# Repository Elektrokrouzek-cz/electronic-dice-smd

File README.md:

# Electronic dice - SMD
This is the construction of electronic dice with SMD components. It is based on ATTINY24A microcontroller.

PCB is 2-layer and was designed using KiCad 9. Fabrication output for JLCPCB is in gerber folder.

Happy soldering!

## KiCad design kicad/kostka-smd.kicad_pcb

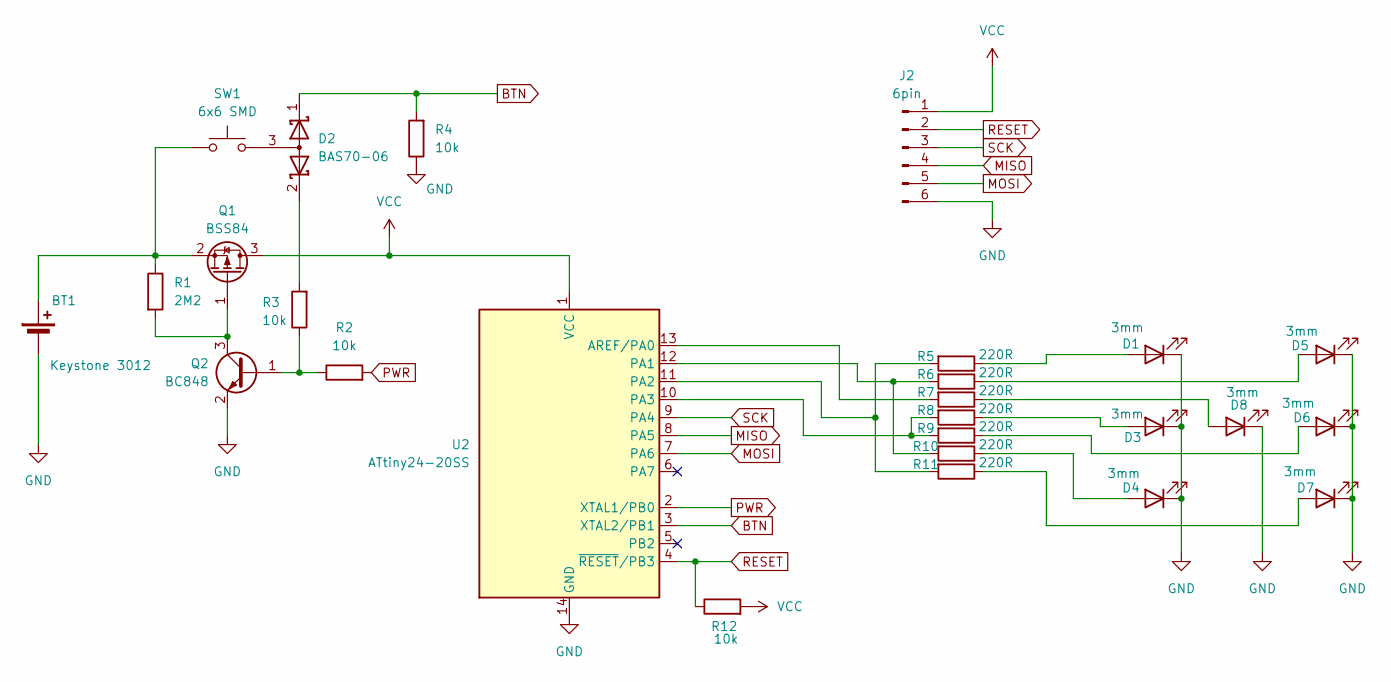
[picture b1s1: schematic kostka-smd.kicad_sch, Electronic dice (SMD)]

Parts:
BT1: Keystone 3012
D1, D3, D4, D5, D6, D7, D8: 3mm; LED_D3.0mm
D2: BAS70-06; SOT-23_Handsoldering
J2: 6pin; PinHeader_1x06_P2.54mm_Vertical
Q1: BSS84; SOT-23_Handsoldering
Q2: BC848; SOT-23_Handsoldering
R1: 2M2; R_1206_3216Metric_Pad1.30x1.75mm_HandSolder
R2, R3, R4, R12: 10k; R_1206_3216Metric_Pad1.30x1.75mm_HandSolder
R5, R6, R7, R8, R9, R10, R11: 220R; R_1206_3216Metric_Pad1.30x1.75mm_HandSolder
SW1: 6x6 SMD; SW_SPST_PTS645
U2: ATtiny24-20SS; SOIC-14_3.9x8.7mm_P1.27mm

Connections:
BTN: D2.1 (K), R4.2, U2.3 (XTAL2/PB1)
GND: BT1.2 (-), D1.1 (K), D3.1 (K), D4.1 (K), D5.1 (K), D6.1 (K), D7.1 (K), D8.1 (K), J2.6, Q2.2 (E), R4.1, U2.14 (GND)
MISO: J2.4, U2.8 (PA5)
MOSI: J2.5, U2.7 (PA6)
unnamed: BT1.1 (+), Q1.2 (S), R1.1, SW1.1
unnamed: D1.2 (A), R5.1
unnamed: D2.3 (A), SW1.2
unnamed: D2.2 (K), R3.2
unnamed: D3.2 (A), R8.1
unnamed: D4.2 (A), R10.1
unnamed: D5.2 (A), R6.1
unnamed: D6.2 (A), R9.1
unnamed: D7.2 (A), R11.1
unnamed: D8.2 (A), R7.1
unnamed: Q1.1 (G), Q2.3 (C), R1.2
unnamed: Q2.1 (B), R2.1, R3.1
unnamed: R7.2, U2.13 (AREF/PA0)
unnamed: R6.2, R10.2, U2.12 (PA1)
unnamed: R5.2, R11.2, U2.11 (PA2)
unnamed: R8.2, R9.2, U2.10 (PA3)
PWR: R2.2, U2.2 (XTAL1/PB0)
RESET: J2.2, R12.1, U2.4 (~RESET/PB3)
SCK: J2.3, U2.9 (PA4)
VCC: J2.1, Q1.3 (D), R12.2, U2.1 (VCC)

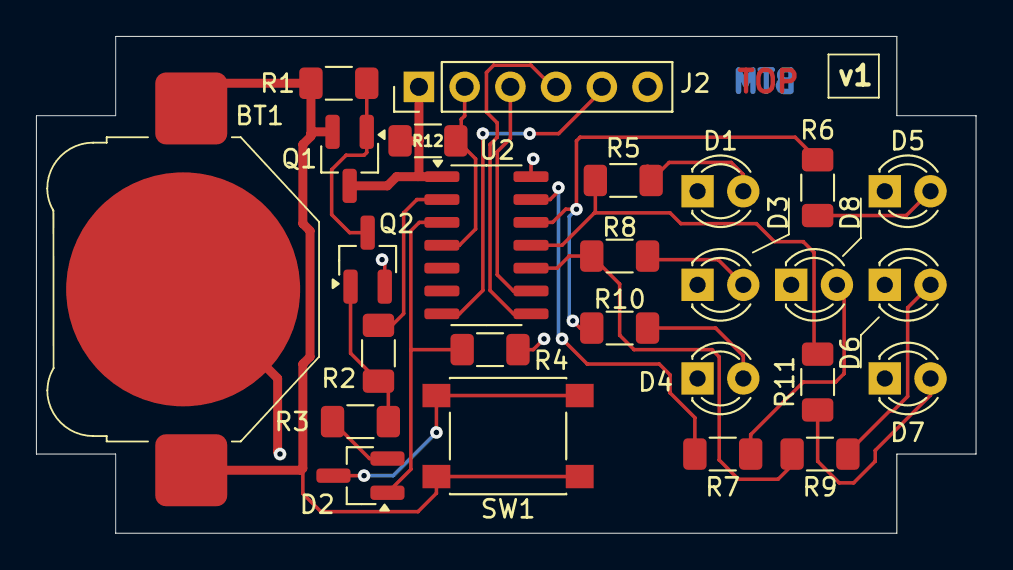
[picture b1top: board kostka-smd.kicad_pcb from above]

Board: 2 copper layers, 52.2 x 27.6 mm, 26 parts (0 on the bottom side), 24 nets.

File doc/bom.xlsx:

Reference | Value | Qty
BT1 | Keystone 3012 | 1
D1,D3,D4,D5,D6,D7,D8 | 3mm | 7
D2 | BAS70-06 | 1
J2 | 6pin | 1
Q1 | BSS84 | 1
Q2 | BC848 | 1
R1 | 2M2 | 1
R2,R3,R4,R12 | 10k | 4
R5,R6,R7,R8,R9,R10,R11 | 220R | 7
SW1 | 6x6 SMD | 1
U2 | ATtiny24-20SS | 1

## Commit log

2025-11-01 Source code and binary added, documentation update
2025-11-01 BOM added
2025-11-04 Construction brief added
2025-11-05 Manual update
